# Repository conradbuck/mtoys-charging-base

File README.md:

# Magical Toys (magicaltoys.com) Charging PCB

This PCB is meant to be used in tandem with their talking stuffed dinosaur as a charging dock to make recharging the dino easier. It is meant to fit into the 3d printed housing in the 3d-files directory.

The PCB uses an op-amp (U1) and shunt resistor in series with the power connectors on the low side to detect when current is flowing through the trace. When a dino stuffed animal is placed on top of the dock, the barrel plug attached to the center connector supplies power to the stuffed animal. The dino charges at 5V at a nominal current of 1.8A. When 1.8A flows across the shunt resistor, it generates a voltage difference of about 0.2V. The op-amp takes in this voltage measurement and compares its difference to Ground at 0V. The op-amp is set to have a threshold of 0.15V. When a voltage greater than that is supplied, it outputs a logical HIGH and turns on the LED at the other end of the PCB. Hence, the LED is only illuminated when the dino is connected to the dock and charging. The LED automatically turns off when the dino is no longer charging or disconnected from the dock.

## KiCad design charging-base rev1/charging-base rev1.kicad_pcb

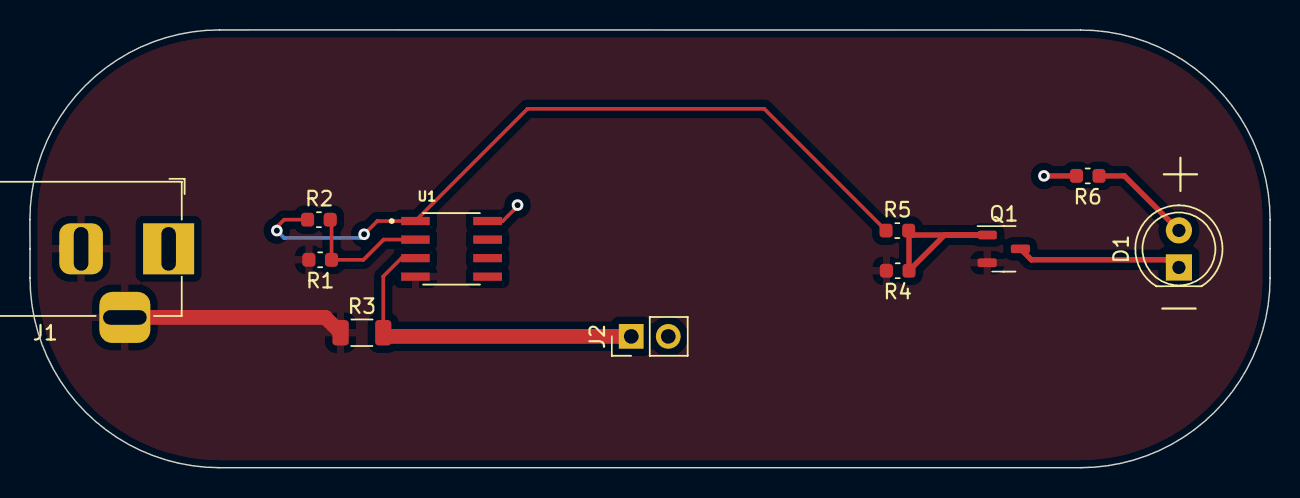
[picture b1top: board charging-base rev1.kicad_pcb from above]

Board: 2 copper layers, 85.0 x 30.0 mm, 11 parts (0 on the bottom side), 8 nets.

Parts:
D1: LED; LED_D5.0mm
J1: Barrel_Jack; BarrelJack_Horizontal
J2: PowerToDino; PinHeader_1x02_P2.54mm_Vertical
Q1: NMOS; SOT-23-3
R1, R4: 10K; C_0603_1608Metric
R2: 1M; C_0603_1608Metric
R3: 250mOhm; R_1206_3216Metric
R5: 10; C_0603_1608Metric
R6: 220; C_0603_1608Metric
U1: LM358_DFN; SOIC127P600X175-8N

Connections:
+VDC: J1.1, J2.2, R6.2, U1.8 (V+)
/output-voltage: R2.2, R5.1, U1.1
GND: J1.2, J1.3, Q1.3 (S), R1.2, R3.1, R4.2, U1.4 (V-)
unnamed: D1.2 (A), R6.1
unnamed: D1.1 (K), Q1.1 (D)
unnamed: J2.1, R3.2, U1.3 (+)
unnamed: Q1.2 (G), R4.1, R5.2
unnamed: R1.1, R2.1, U1.2 (-)

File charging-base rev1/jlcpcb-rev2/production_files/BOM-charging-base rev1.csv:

Comment,Designator,Footprint,LCSC
35mOhm,R3,R_1206_3216Metric,C5185598
10K,R4,C_0603_1608Metric,
PowerToDino,J2,PinHeader_1x02_P2.54mm_Vertical,
1M,R2,C_0603_1608Metric,
Barrel_Jack,J1,BarrelJack_Horizontal,C136744
LED,D1,LED_D5.0mm,C883178
220,R6,C_0603_1608Metric,
10K,R1,C_0603_1608Metric,
10,R5,C_0603_1608Metric,
LM358_DFN,U1,DFN-8-1EP_2x2mm_P0.5mm_EP1.05x1.75mm,C9418
NMOS,Q1,SOT-23-3,C347475

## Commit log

2024-11-24 added blank pcb files
2024-11-24 added op-amp and nmos to schem
2024-11-24 added some power questions
2024-11-24 finished rev1 of layout, resistor sensor not yet selected
2024-11-24 added barrel plug source, changed footprint U1
2024-11-24 added rev3 manufacturing files
2024-11-24 added op-amp guide
2024-11-24 added pic of pcb
2024-12-10 added 3d files and pic to readme
2024-12-10 fixed pic of pcb
2024-12-10 identified op-amp in readme
